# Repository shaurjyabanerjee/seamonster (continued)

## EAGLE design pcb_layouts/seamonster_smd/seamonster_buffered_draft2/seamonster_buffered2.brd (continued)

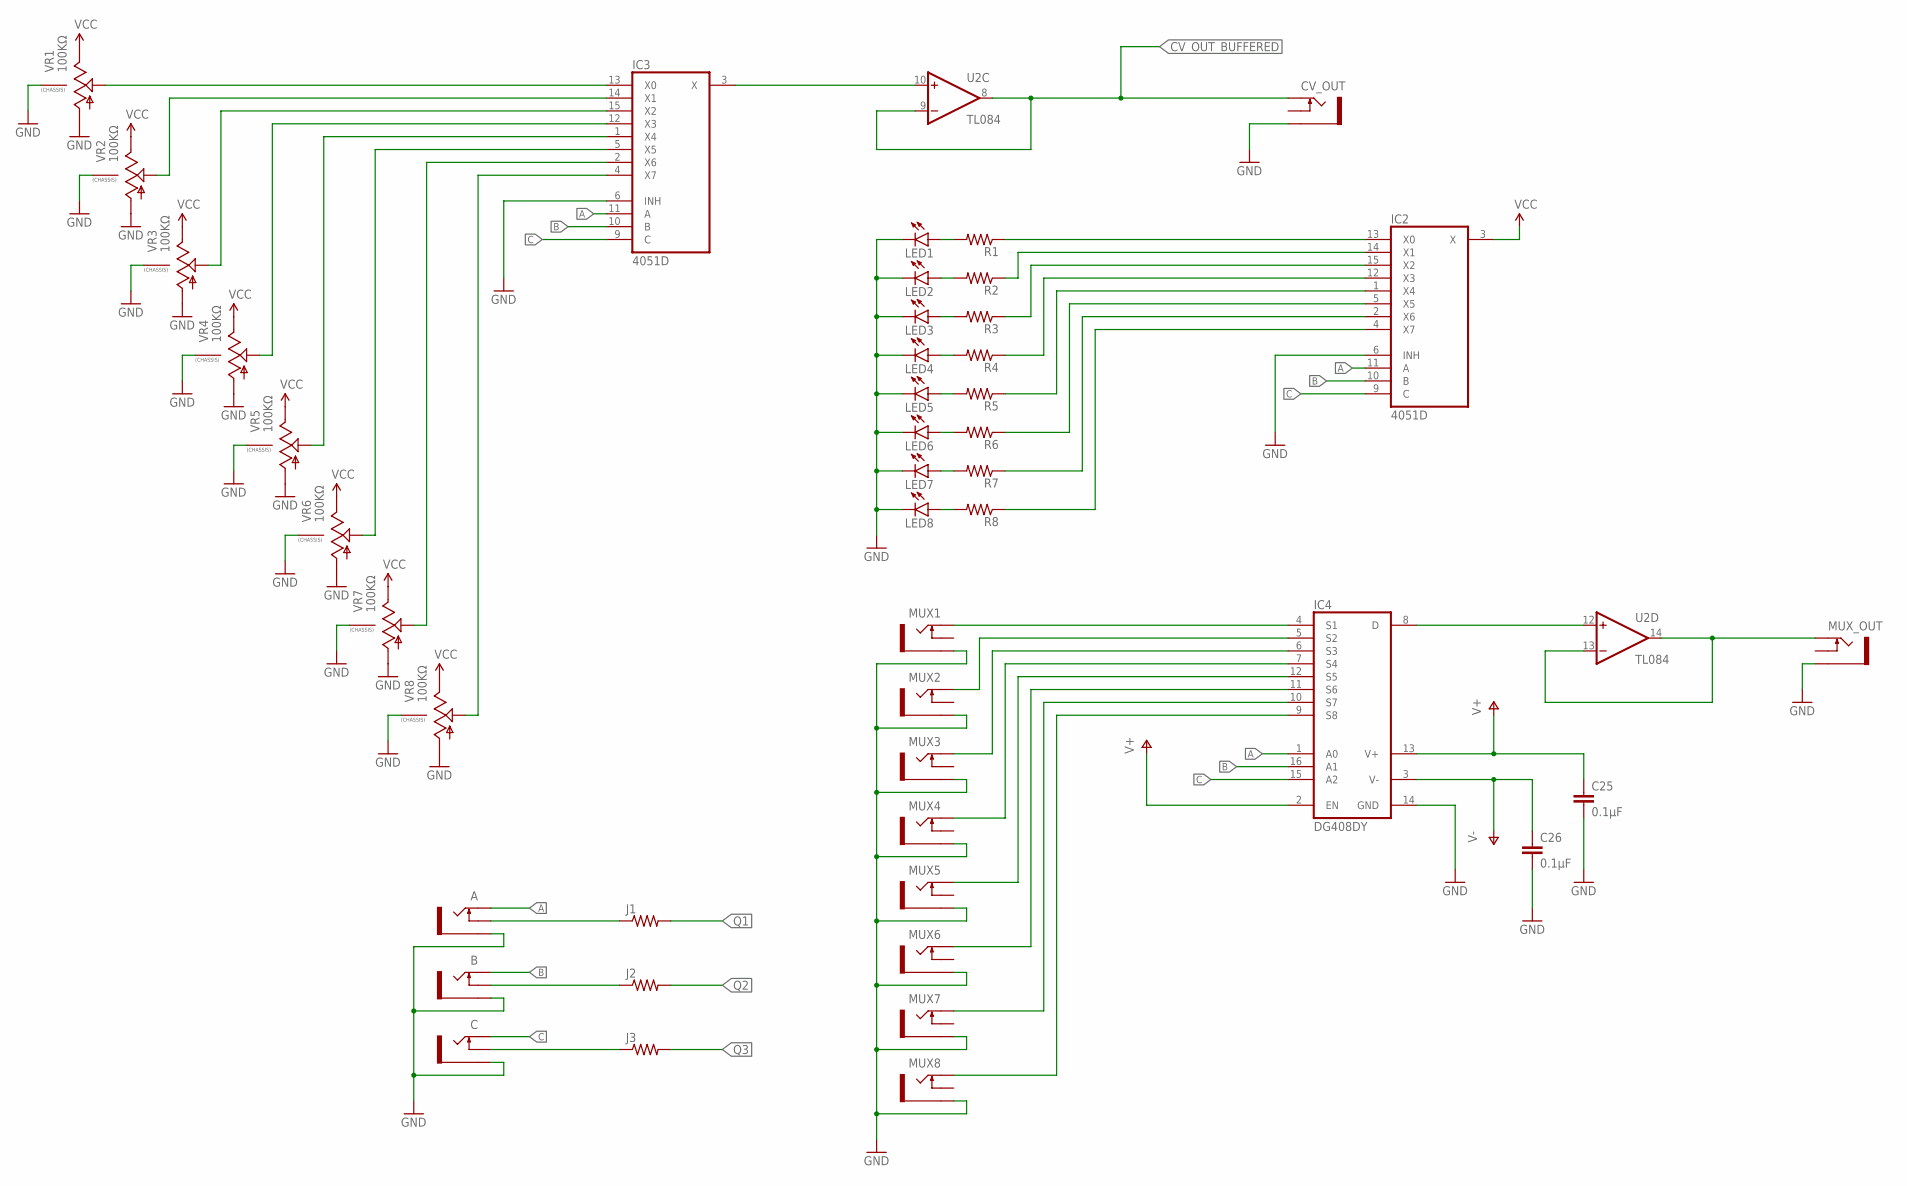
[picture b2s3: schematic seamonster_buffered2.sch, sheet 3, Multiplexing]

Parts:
A: THONKICONNNEW; WQP-PJ301M-12_JACK
B: THONKICONNNEW; WQP-PJ301M-12_JACK
C: THONKICONNNEW; WQP-PJ301M-12_JACK
C25, C26: 0.1µF; 0805
CV_OUT: THONKICONNNEW; WQP-PJ301M-12_JACK
IC2, IC3: 4051D; SO16
IC4: DG408DY; SO16
J1, J2, J3: RESISTOR0805-RES; 0805
LED1, LED2, LED3, LED4, LED5, LED6, LED7, LED8: LED3MM
MUX1, MUX2, MUX3, MUX4, MUX5, MUX6, MUX7, MUX8: THONKICONNNEW; WQP-PJ301M-12_JACK
MUX_OUT: THONKICONNNEW; WQP-PJ301M-12_JACK
R1, R2, R3, R4, R5, R6, R7, R8: RESISTOR0805-RES; 0805
U2: TL084; SO14
VR1, VR2, VR3, VR4, VR5, VR6, VR7, VR8: 100KΩ; 9MM_SNAP-IN_POT

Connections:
A: A.P$1_TIP (TIP), IC2.11 (A), IC3.11 (A), IC4.1 (A0)
B: B.P$1_TIP (TIP), IC2.10 (B), IC3.10 (B), IC4.16 (A1)
C: C.P$1_TIP (TIP), IC2.9 (C), IC3.9 (C), IC4.15 (A2)
CV_OUT: IC3.3 (X), U2.10 (+IN)
CV_OUT_BUFFERED: CV_OUT.P$1_TIP (TIP), U2.8 (OUT), U2.9 (-IN); also elsewhere on the board
MUX1: IC4.4 (S1), MUX1.P$1_TIP (TIP)
MUX2: IC4.5 (S2), MUX2.P$1_TIP (TIP)
MUX3: IC4.6 (S3), MUX3.P$1_TIP (TIP)
MUX4: IC4.7 (S4), MUX4.P$1_TIP (TIP)
MUX5: IC4.12 (S5), MUX5.P$1_TIP (TIP)
MUX6: IC4.11 (S6), MUX6.P$1_TIP (TIP)
MUX7: IC4.10 (S7), MUX7.P$1_TIP (TIP)
MUX8: IC4.9 (S8), MUX8.P$1_TIP (TIP)
unnamed: IC4.8 (D), U2.12 (+IN)
unnamed: MUX_OUT.P$1_TIP (TIP), U2.13 (-IN), U2.14 (OUT)
unnamed: LED1.A, R1.2
unnamed: LED2.A, R2.2
unnamed: LED3.A, R3.2
unnamed: LED4.A, R4.2
unnamed: LED5.A, R5.2
unnamed: LED6.A, R6.2
unnamed: LED7.A, R7.2
unnamed: LED8.A, R8.2
unnamed: IC3.13 (X0), VR1.2 (S)
unnamed: IC2.13 (X0), R1.1
unnamed: IC2.14 (X1), R2.1
unnamed: IC2.15 (X2), R3.1
unnamed: IC2.12 (X3), R4.1
unnamed: IC2.1 (X4), R5.1
unnamed: IC2.5 (X5), R6.1
unnamed: IC2.2 (X6), R7.1
unnamed: IC2.4 (X7), R8.1
unnamed: IC3.14 (X1), VR2.2 (S)
unnamed: IC3.15 (X2), VR3.2 (S)
unnamed: IC3.12 (X3), VR4.2 (S)
unnamed: IC3.1 (X4), VR5.2 (S)
unnamed: IC3.5 (X5), VR6.2 (S)
unnamed: IC3.2 (X6), VR7.2 (S)
unnamed: IC3.4 (X7), VR8.2 (S)
unnamed: A.P$2_SWITCH (SWITCH), J1.1
unnamed: B.P$2_SWITCH (SWITCH), J2.1
unnamed: C.P$2_SWITCH (SWITCH), J3.1
Q1: J1.2; also elsewhere on the board
Q2: J2.2; also elsewhere on the board
Q3: J3.2; also elsewhere on the board
V+: C25.1, IC4.2 (EN), IC4.13 (V+); also elsewhere on the board
V-: C26.1, IC4.3 (V-); also elsewhere on the board
VCC: IC2.3 (X), VR1.3 (E), VR2.3 (E), VR3.3 (E), VR4.3 (E), VR5.3 (E), VR6.3 (E), VR7.3 (E), VR8.3 (E); also elsewhere on the board

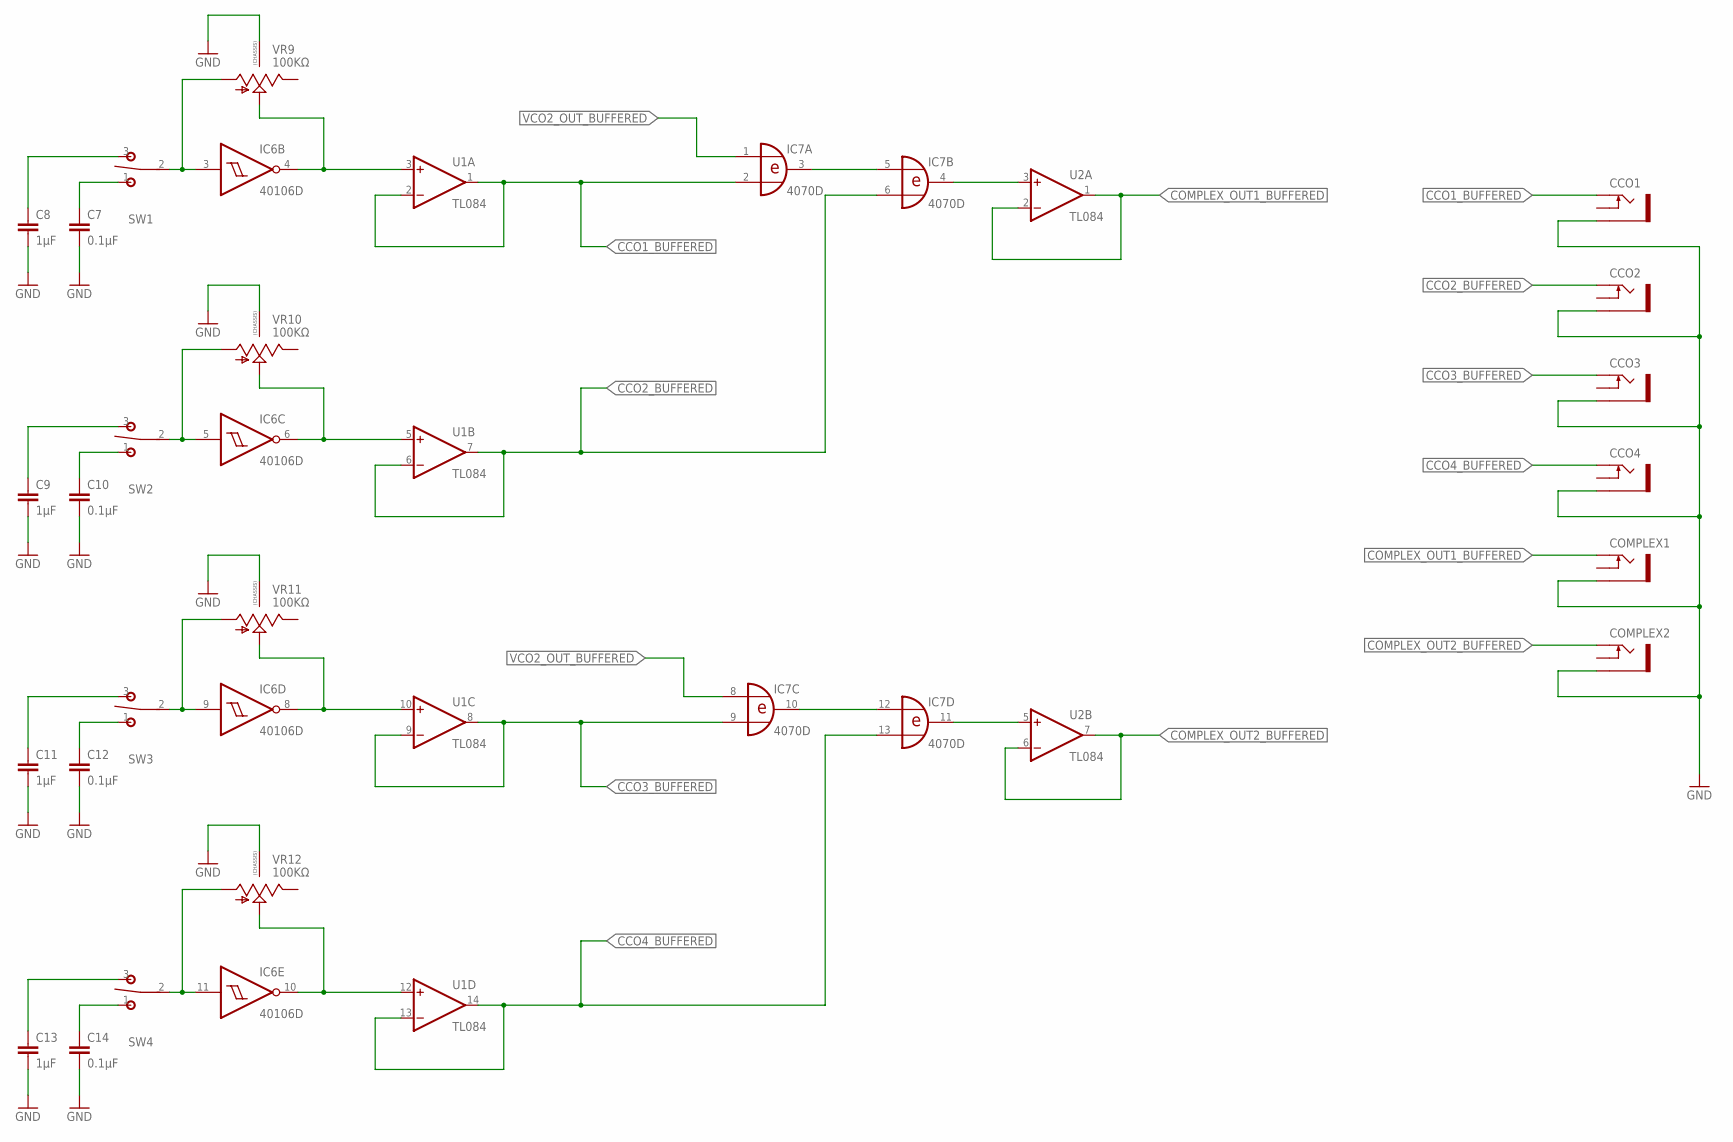
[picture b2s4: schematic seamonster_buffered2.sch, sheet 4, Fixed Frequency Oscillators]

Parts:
C7, C10, C12, C14: 0.1µF; 0805
C8, C9, C11, C13: 1µF; 0805
CCO1, CCO2, CCO3, CCO4: THONKICONNNEW; WQP-PJ301M-12_JACK
COMPLEX1, COMPLEX2: THONKICONNNEW; WQP-PJ301M-12_JACK
IC6: 40106D; SO14
IC7: 4070D; SO14
SW1, SW2, SW3, SW4: SPDT ON-ON; M9040P
U1, U2: TL084; SO14
VR9, VR10, VR11, VR12: 100KΩ; 9MM_SNAP-IN_POT

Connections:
CCO1_BUFFERED: CCO1.P$1_TIP (TIP), IC7.2 (I1), U1.1 (OUT), U1.2 (-IN)
CCO2_BUFFERED: CCO2.P$1_TIP (TIP), IC7.6 (I1), U1.6 (-IN), U1.7 (OUT)
CCO3_BUFFERED: CCO3.P$1_TIP (TIP), IC7.9 (I1), U1.8 (OUT), U1.9 (-IN)
CCO4_BUFFERED: CCO4.P$1_TIP (TIP), IC7.13 (I1), U1.13 (-IN), U1.14 (OUT)
COMPLEX_OUT1_BUFFERED: COMPLEX1.P$1_TIP (TIP), U2.1 (OUT), U2.2 (-IN)
COMPLEX_OUT2_BUFFERED: COMPLEX2.P$1_TIP (TIP), U2.6 (-IN), U2.7 (OUT)
INV_B_IN: IC6.3 (I), SW1.2, VR9.1 (A)
INV_B_OUT: IC6.4 (O), U1.3 (+IN), VR9.2 (S)
INV_C_IN: IC6.5 (I), SW2.2, VR10.1 (A)
INV_C_OUT: IC6.6 (O), U1.5 (+IN), VR10.2 (S)
INV_D_IN: IC6.9 (I), SW3.2, VR11.1 (A)
INV_D_OUT: IC6.8 (O), U1.10 (+IN), VR11.2 (S)
INV_E_IN: IC6.11 (I), SW4.2, VR12.1 (A)
INV_E_OUT: IC6.10 (O), U1.12 (+IN), VR12.2 (S)
unnamed: IC7.3 (O), IC7.5 (I0)
unnamed: IC7.10 (O), IC7.12 (I0)
unnamed: IC7.4 (O), U2.3 (+IN)
unnamed: IC7.11 (O), U2.5 (+IN)
unnamed: C7.1, SW1.1 (O)
unnamed: C8.1, SW1.3 (S)
unnamed: C10.1, SW2.1 (O)
unnamed: C9.1, SW2.3 (S)
unnamed: C12.1, SW3.1 (O)
unnamed: C11.1, SW3.3 (S)
unnamed: C14.1, SW4.1 (O)
unnamed: C13.1, SW4.3 (S)
VCO2_OUT_BUFFERED: IC7.1 (I0), IC7.8 (I0); also elsewhere on the board

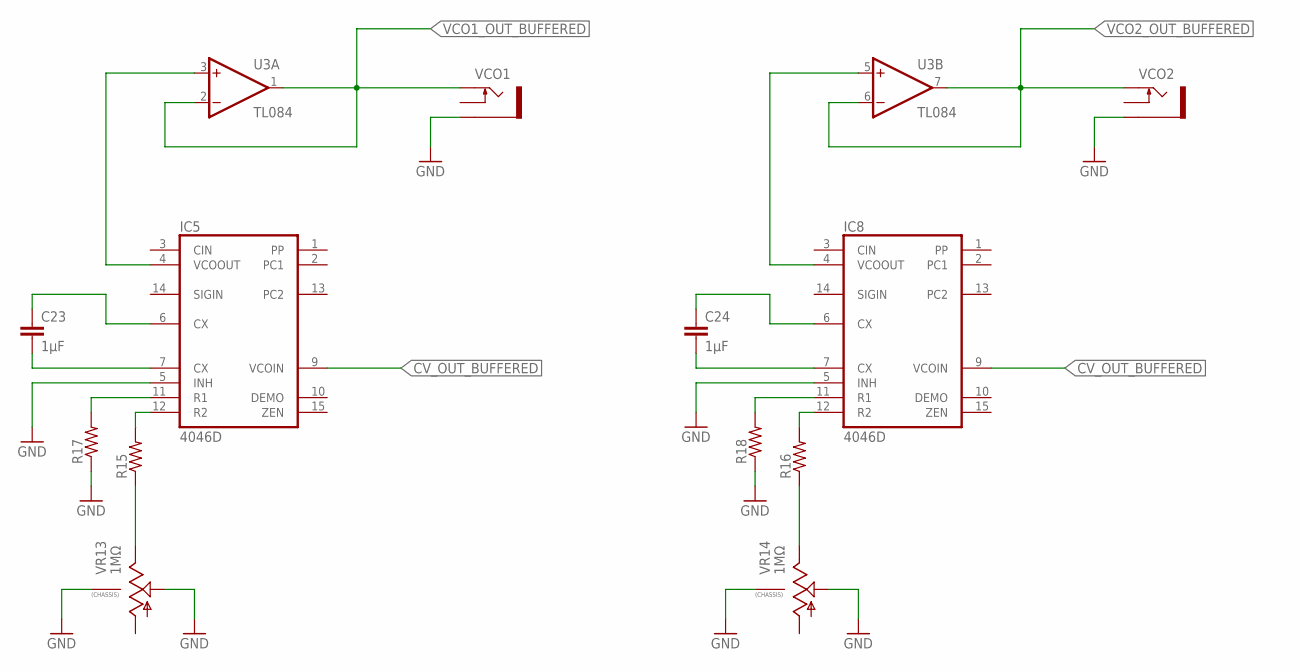
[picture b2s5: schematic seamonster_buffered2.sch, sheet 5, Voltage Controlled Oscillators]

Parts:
C23, C24: 1µF; 0805
IC5, IC8: 4046D; SO16
R15, R16, R17, R18: RESISTOR0805-RES; 0805
U3: TL084; SO14
VCO1, VCO2: THONKICONNNEW; WQP-PJ301M-12_JACK
VR13, VR14: 1MΩ; 9MM_SNAP-IN_POT

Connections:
CV_OUT_BUFFERED: IC5.9 (VCOIN), IC8.9 (VCOIN); also elsewhere on the board
unnamed: IC5.12 (R2), R15.2
unnamed: R15.1, VR13.3 (E)
unnamed: C23.1, IC5.6 (CX)
unnamed: C23.2, IC5.7 (CX)
unnamed: C24.1, IC8.6 (CX)
unnamed: C24.2, IC8.7 (CX)
unnamed: IC8.12 (R2), R16.2
unnamed: R16.1, VR14.3 (E)
unnamed: IC8.11 (R1), R18.2
unnamed: IC5.11 (R1), R17.2
VCO1_OUT: IC5.4 (VCOOUT), U3.3 (+IN)
VCO1_OUT_BUFFERED: U3.1 (OUT), U3.2 (-IN), VCO1.P$1_TIP (TIP)
VCO2_OUT: IC8.4 (VCOOUT), U3.5 (+IN)
VCO2_OUT_BUFFERED: U3.6 (-IN), U3.7 (OUT), VCO2.P$1_TIP (TIP); also elsewhere on the board

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
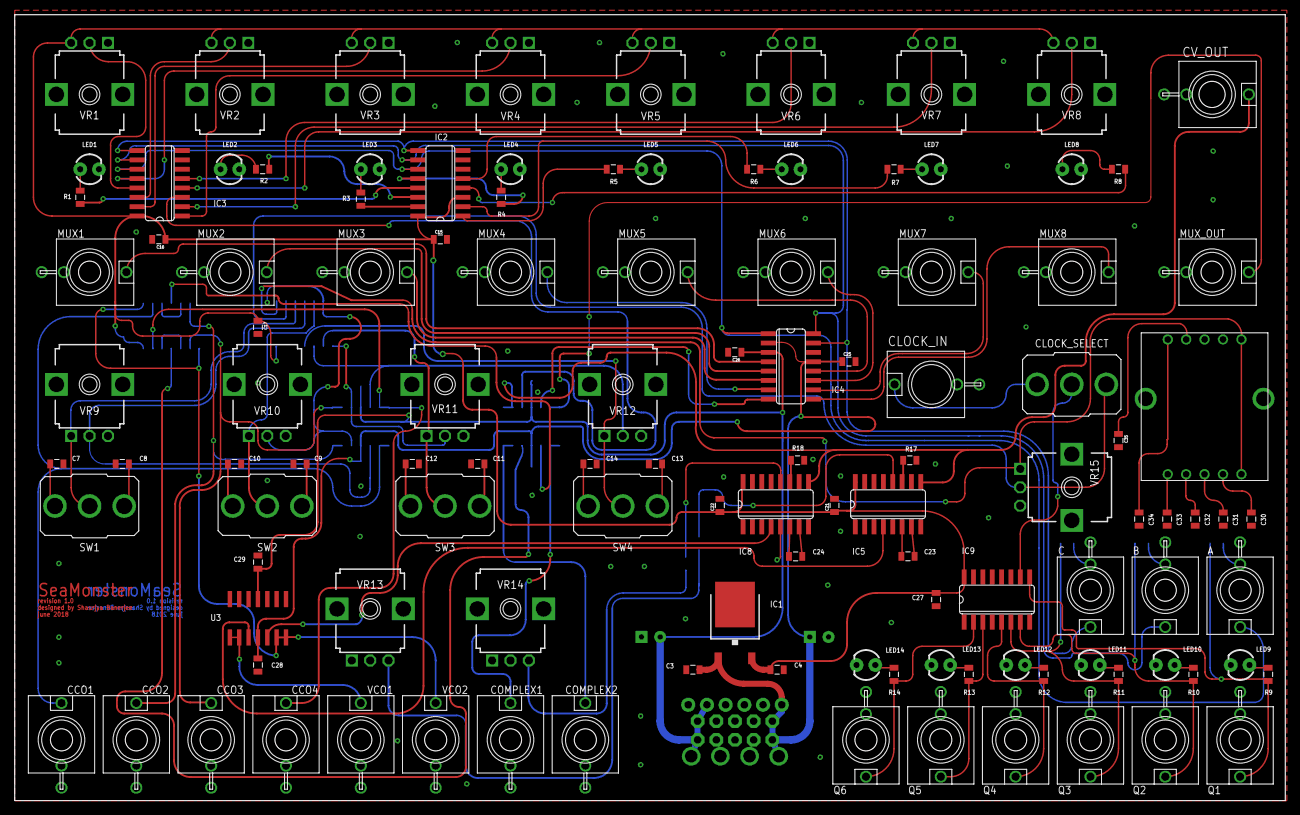
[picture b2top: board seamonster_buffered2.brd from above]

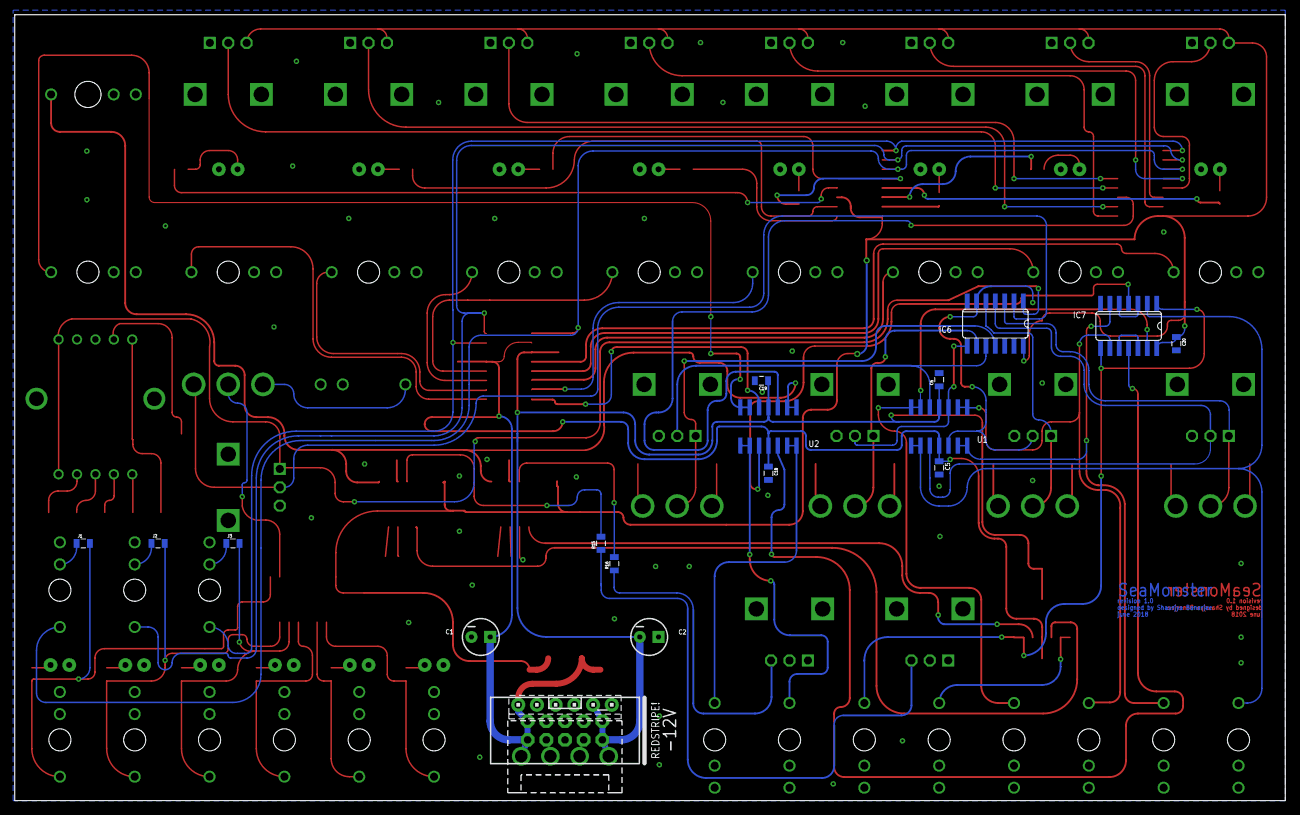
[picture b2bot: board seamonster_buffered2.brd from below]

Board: 2 copper layers, 172.5 x 106.7 mm, 132 parts (17 on the bottom side), 108 nets.

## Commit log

2017-07-05 inital commit
2017-07-10 added new panel drill files for prototype panel
2017-07-11 made new folder for buffered seamonster
2017-07-11 figured out invoking across multiple sheets
2017-07-12 fleshed out schematic pages
2017-07-13 added in VCOs and more buffering
2017-07-13 roughly positioned thruhole panel parts
2017-07-14 roughly placed all remaining parts
2017-07-14 added top and bottom layer ground pours, did basic layout
2017-07-14 routed ABC bus between 4051s, more basic routing
2017-07-16 made folder for panel files, created pours and dimension layer
2017-07-16 added prototypinh photos
2017-07-16 added drill positions to panel for pots, mux and outs
2017-07-17 added jumpers for normalled ABC bus operation
2017-07-17 created v2 buffered board, moved ICs
2017-07-17 made and custom part for 8 way Alpha rotary switch as clock speed selector
2017-07-17 routed power nets, moved ICs
2017-07-18 routed 408 MUX power and most IO
2017-07-18 finished routing IO to DG408 MUX
2017-07-18 cleaned up silkscreen
2017-07-18 finished routing ABC bus to jacks, began routing oscillators
2017-07-18 misc routing for oscillators and buffers
2017-07-20 routed bipolar power to buffers, and buffered cv out
2017-07-20 more misc buffer and XOR routing
2017-07-20 connected power nets up, moved and routed VCOs
2017-07-23 added to-do text file for PCB revisions
2018-09-28 finished routing, working on silkscreen
2018-10-15 worked on ai panel mockup, added TH capacitor optionally
2019-03-12 smd mk1 routing complete
